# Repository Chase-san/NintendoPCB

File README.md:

# NintendoPCB

This repository is for the reproduction and documentation of various Nintendo PCBs. Specifically targeting the Gameboy series of handheld consoles.

# License

These boards are released under the Creative Commons Attribution-NonCommercial-ShareAlike 4.0 International License. See the LICENSE for more details.

In short, don't sell these designs or boards produced from these designs, and do attribute the designs to me.

# Gameboy GamePak PCB Designs

At present these are designed as repair boards for the official Nintendo Gameboy games. The intention is for the components from the original pcb to be transplanted directly to these boards. However a list of parts is made available if these are not otherwise available. These boards are designed to closely replicate the original tracks and fill zones of the original. These do NOT have the intention of fooling others into thinking they are official boards.

These are NOT designed to be used for Flash Carts, but rather to repair official games.
Please see HDR's [MBC3-Flashcart](https://github.com/HDR/MBC3-Flashcart) and [MBC30-Flashcart](https://github.com/HDR/MBC30-Flashcart) for PCB designs useful as flashcarts.

## Nintendo Board ID

Nintendo uses roughly the following system for producing the ID for a board.

`SYSTEM-ID-REVISION`

`SYSTEM` is either DMG or more rarely GBC, referring to the original Gameboy or the Gameboy Color.

`ID` is the actual ID of the board.

`REVISION` is the revision of the board. Most boards only have a single revision in the wild, but others, such as the DMG-BEAN have up to 6. Every revision I have seen has been electronically compatible with minor track, via, or fill differences.

## Differences from Official PCB

Each of these may have several revisions by Nintendo, I will usually try to base my board off the latest revision where possible. Despite this there are significant differences in design in a few regards compared to official PCBS.

### Debug Tracks and Holes

The Official PCBs make use of tracks which are interconnected, but which are then drilled out. I am unsure of the exact purpose of these, but they were likely for grounding purposes during manufacturing. Most of these have been removed as they serve no purposes for the repair board.
While it is possible that these extra tracks may allow special RF interactions, this does not appear to be by design.

### Thermal Relief

The Official PCBs make use of a different thermal relief pattern than KiCAD. Replicating the factory thermal relief pattern is possible but time consuming. Therefore these are often changed to the method KiCAD uses. Additionally some components may have had thermal relief added where it may be reasonable to do so.

### Identifying Marks

Some of these have been removed or altered.

- The revision number has been changed from a two digit number to "R#" where # is the repair board revision.
- The text "Repair Board" has been added near the board identifier.
- My initials and the year and month of the design have been added.
- Some non-informative identifying marks have been removed. Such as the large numbers on the front of the boards and the circle markers for the date identifier boxes.

### Tracks and Fill

While I make an effort to closely replicate the original board, some features may not be identical to the original. Some features are non-trivial to replicate and therefore an approximation has been used instead.

The main example of this being the battery fill which is fully circular on the repair boards.

## Ordering / Using the Gerber Files

I highly recommend using a service such as [JLCPCB](https://jlcpcb.com/) to get these manufactured. The following are the options that should be selected.

- Layers: 2
- Dimensions: 51mm x 60.7mm / 2" x 2.39"
- PCB Thickness: 0.8mm / 0.0315" (required)
- Surface Finish: ENIG or Hard Gold (required)
- Gold Fingers: Yes (required)
- Finger Chamfer: 45° (recommended)
- Copper Weight: 1 oz or higher (recommended)
- Color: Green (suggested), other colors have longer lead times

Of note, Hard Gold is very expensive so ENIG is a good option. The thicker the layer of gold the better the longer the pins will last. A heavier copper weight is nice but not required.

## Board List

These are the boards. Please check your original for the required one. Only boards with a revision number have a repair board developed.

Each folder related to this project is a distinct KiCAD project, containing subfolders with images of the repair board and scans of the original board it was based on.

This list is NOT exhaustive.

| Revision | ID       | MBC    | ROM      | RAM      | Battery | Other        |
| :------: | :------- | :----: | :----:   | :------: | :-----: | :----------- |
|          | CGB-A32  | MBC-6  | SOP-32   | SOP-28   | CR1616  | Flash        |
| [R3](https://github.com/Chase-san/NintendoPCB/releases/tag/dmg-a02-r3) | DMG-A02  | MBC-5  | SOP-32   | SOP-28   | CR1616  |              |
|          | DMG-A03  | MBC-5  | TSOP2-44 | SOP-28   | CR1616  |              |
|          | DMG-A04  | MBC-5  | TSOP-32  | SOP-28   | CR1616  | Rumble       |
|          | DMG-A06  | MBC-5  | SOP-32   | SOP-28   | CR1616  |              |
|          | DMG-A07  | MBC-5  | SOP-32   | N/A      | N/A     |              |
|          | DMG-A08  | MBC-5  | TSOP2-44 | SOP-28   | CR1616  |              |
|          | DMG-A09  | MBC-5  | TSOP2-44 | N/A      | N/A     |              |
|          | DMG-A11  | MBC-5  | TSOP2-44 | SOP-28   | CR1616  | Rumble       |
|          | DMG-A14  | MBC-5  | TSOP2-44 | SOP-28   | CR2025  |              |
|          | DMG-A15  | MBC-5  | TSOP2-44 | SOP-28   | CR2025  | 2x ROM       |
|          | DMG-A16  | MBC-5  | SOP-32   | SOP-32   | CR2025  |              |
|          | DMG-A40  | MBC-7  | SOP-32   | N/A      | N/A     | Tilt/EEPROM  |
|          | DMG-A47  | MBC-7  | TSOP2-44 | N/A      | N/A     | Tilt/EEPROM  |
| [R1](https://github.com/Chase-san/NintendoPCB/releases/tag/dmg-aaa-r1) | DMG-AAA  | N/A    | MQFP-44  | N/A      | N/A     |              |
|          | DMG-BBA  | MBC-1  | SOIC-24  | N/A      | N/A     |              |
|          | DMG-BEAN | MBC-1  | SOP-32   | N/A      | N/A     |              |
|          | DMG-BFAN | MBC-1  | SOP-32   | N/A      | N/A     |              |
|          | DMG-DECN | MBC-1  | SOP-32   | SOP-28   | CR1616  |              |
|          | DMG-DEDN | MBC-1  | SOP-32   | SOP-28   | CR1616  |              |
|          | DMG-DGCU | MBC-1  | TSOP2-44 | SOP-28   | CR1616  |              |
| [R1](https://github.com/Chase-san/NintendoPCB/releases/tag/dmg-gdan-r1) | DMG-GDAN | MBC-2  | SOP-32   | SOP-28   | CR1616  |              |
|          | DMG-KECN | MBC-3  | SOP-32   | SOP-28   | CR2025  | Clock        |
|          | DMG-KFCN | MBC-3  | SOP-32   | SOP-28   | CR2025  | Clock        |
|          | DMG-KFDN | MBC-3  | SOP-32   | SOP-28   | CR2025  | Clock        |
| [R4](https://github.com/Chase-san/NintendoPCB/releases/tag/dmg-kgdu-r4) | DMG-KGDU | MBC-3  | TSOP2-44 | SOP-28   | CR2025  | Clock        |
|          | DMG-LFDN | MBC-3  | SOP-32   | SOP-28   | CR2025  | Clock        |
|          | DMG-MHEU | MBC-30 | TSOP2-44 | SOP-28   | CR2025  | Clock        |
|          | DMG-TEDN | HuC-1  | SOP-32   | SOP-28   | CR1616  | IR           |
|          | DMG-TFDN | HuC-1  | SOP-32   | SOP-28   | CR1616  | IR           |
|          | DMG-UEDT | HuC-3  | TSOP1-32 | TSOP1-28 | CR2025  | IR/Clock     |
|          | DMG-UFDT | HuC-3  | TSOP1-32 | TSOP1-28 | CR2025  | IR/Clock     |
|          | DMG-UGDU | HuC-3  | TSOP2-44 | TSOP1-28 | CR2025  | IR/Clock     |
|          | DMG-Z02  | MBC-5  | SOP-32   | SOP-28   | CR1616  |              |
|          | DMG-Z03  | MBC-5  | TSOP2-44 | SOP-28   | CR1616  |              |
|          | DMG-Z04  | MBC-5  | TSOP2-44 | SOP-28   | CR1616  | Rumble       |

# Game Usage

Here is a list of the primary games using the given boards. Some boards have a lot of games or the game that uses the board is not particularly popular. Some games have used multiple boards (mostly pokemon).

| ID        | Main Usage  |
| :-------  | :---------  |
| CGB-A32   | Net de Get - Minigame @ 100 (Japan) |
| DMG-A02   | Pokemon Red/Blue, Lots of other games. |
| DMG-A03   | Wario Land 2/3 |
| DMG-A04   | Pokemon Pinball |
| DMG-A06   | Game & Watch, Mega Man Xtreme 2 |
| DMG-A07   |  |
| DMG-A08   | TLOZ: Oracle of Ages/Seasons  |
| DMG-A09   | Rayman, Tony Hawk Pro Skater 2 |
| DMG-A11   | Pokemon Pinball  |
| DMG-A14   |  |
| DMG-A15   |  |
| DMG-A16   |  |
| DMG-A40   | Kirby Tilt & Tumble  |
| DMG-A47   |  |
| DMG-AAA   | Catrap, Dr. Mario, Tetris  |
| DMG-BBA   |  |
| DMG-BEAN  | Mega Man II-V, Pacman |
| DMG-BFAN  | Mortal Kombat I/II |
| DMG-DECN  | Donkey Kong, Donkey Kong Land, Super Mario Land 2  |
| DMG-DEDN  | Pocket Monsters Aka, Midori (Japan) |
| DMG-DGCU  | Dragon Quest Monsters  |
| DMG-GDAN  | Kirby's Pinball Land |
| DMG-KECN  | Bokujou Monogatari GB  |
| DMG-KFCN  | Mary Kate & Ashley Pocket Planner |
| DMG-KFDN  | Pokemon Gold/Silver/Crystal  |
| DMG-KGDU  | Pokemon Gold/Silver/Crystal  |
| DMG-LFDN  | Pocket Monsters Pikachu (Japan) |
| DMG-MHEU  | Pokemon Crystal (Japan)  |
| DMG-TEDN  | Pocket Bomber Man (Japan) |
| DMG-TFDN  | Pokemon Card GB (Japan) |
| DMG-UEDT  | Pocket Family GB  |
| DMG-UFDT  | Pocket Family GB  |
| DMG-UGDU  | Pocket Family GB 2  |
| DMG-Z02   | Mega Man Xtreme |
| DMG-Z03   |  |
| DMG-Z04   | Pokemon Pinball  |

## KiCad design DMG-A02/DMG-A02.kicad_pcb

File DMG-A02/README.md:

# DMG-A02

This board is a repair board based on the DMG-A02-10. The DMG-A02 is used by german versions of Pokemon Red/Blue, as well as Pokemon Yellow, Pokemon Trading Card Game, and Link's Awakening DX.

The original featured cut holes that were used for debugging purposes, most of these have been omitted.

This board was designed to closely replicate the footprints and routes used by the original cartridge board. All components may be sourced from an original cart.

## Components

This board features a 32-pin ROM and a 28-pin RAM module.

| Ref   | Package     | Description  | Notes | 
| :---: | :---------: | :----------- | :---- |
| U1    | SSOP-32W    | Program ROM  | ~11mm wide |
| U2    | LQFP-32     | MBC-5        | |
| U3    | SOIC-28W    | SRAM         | ~8.3mm wide |
| U4    | SOIC-28     | System Reset | ~4.3mm wide |
| C1, C2, C3, C4 | 0603 (in)   |  0.015uF - 0.1uF Capacitor | |
| C5    | 0603 (in)   | Empty | |
| C6    | 0603 (in)   | 33pF Capacitor | May be left empty |
| R1    | 0603 (in)   | 1kOhm Resistor | |

## Change Log

### R4 (2023-02-13)
- Added teardrop to pin pads.
- Adjusted MBC cutout
- Other minor changes

### R3 (2023-01-23)
- Added teardrops to via.
- Fillet tracks
- Added MBC hole

### Rev2 (2023-01-21)
- Fixed rear GND Test pad.

### Rev1 (2023-01-20)
- Initial build

## Images

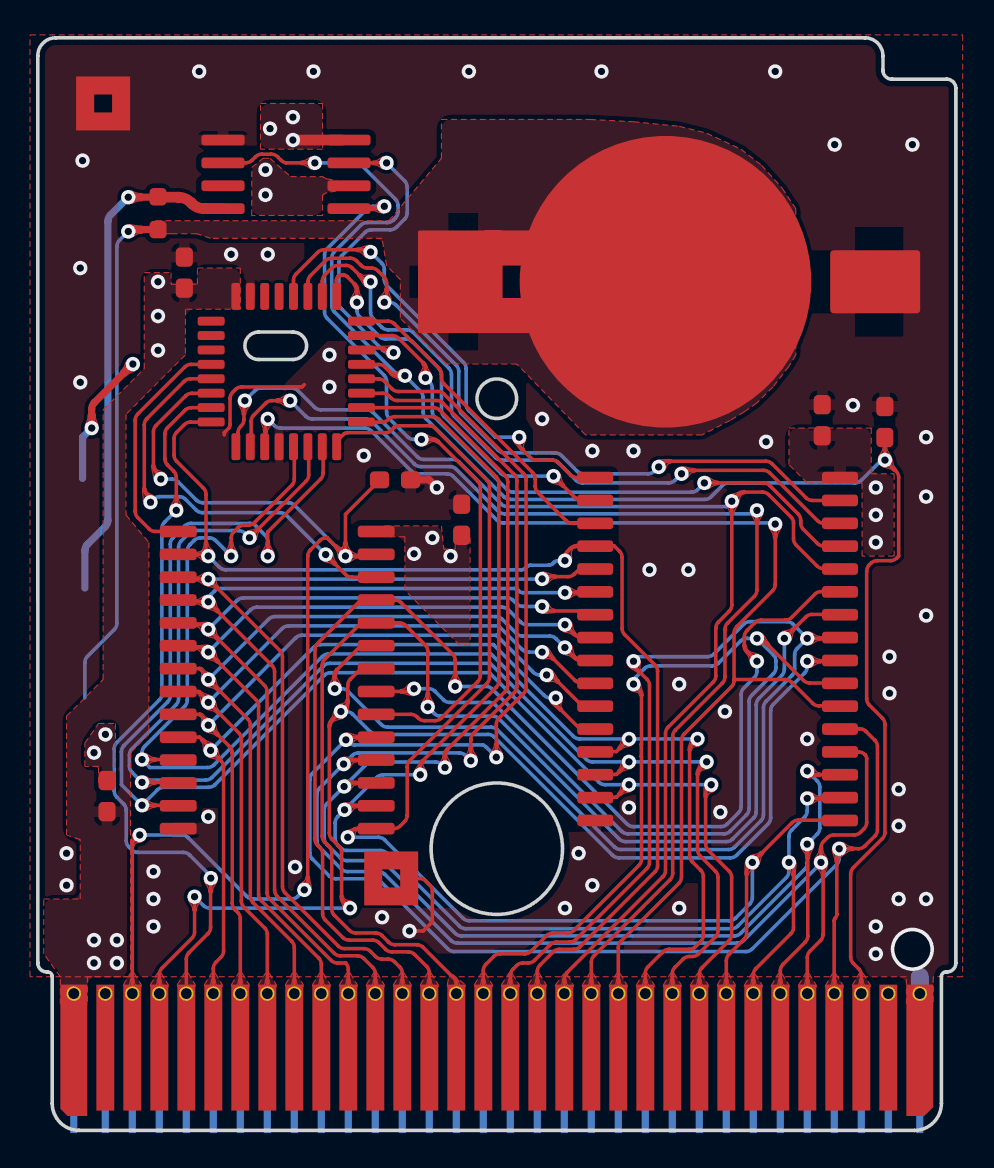
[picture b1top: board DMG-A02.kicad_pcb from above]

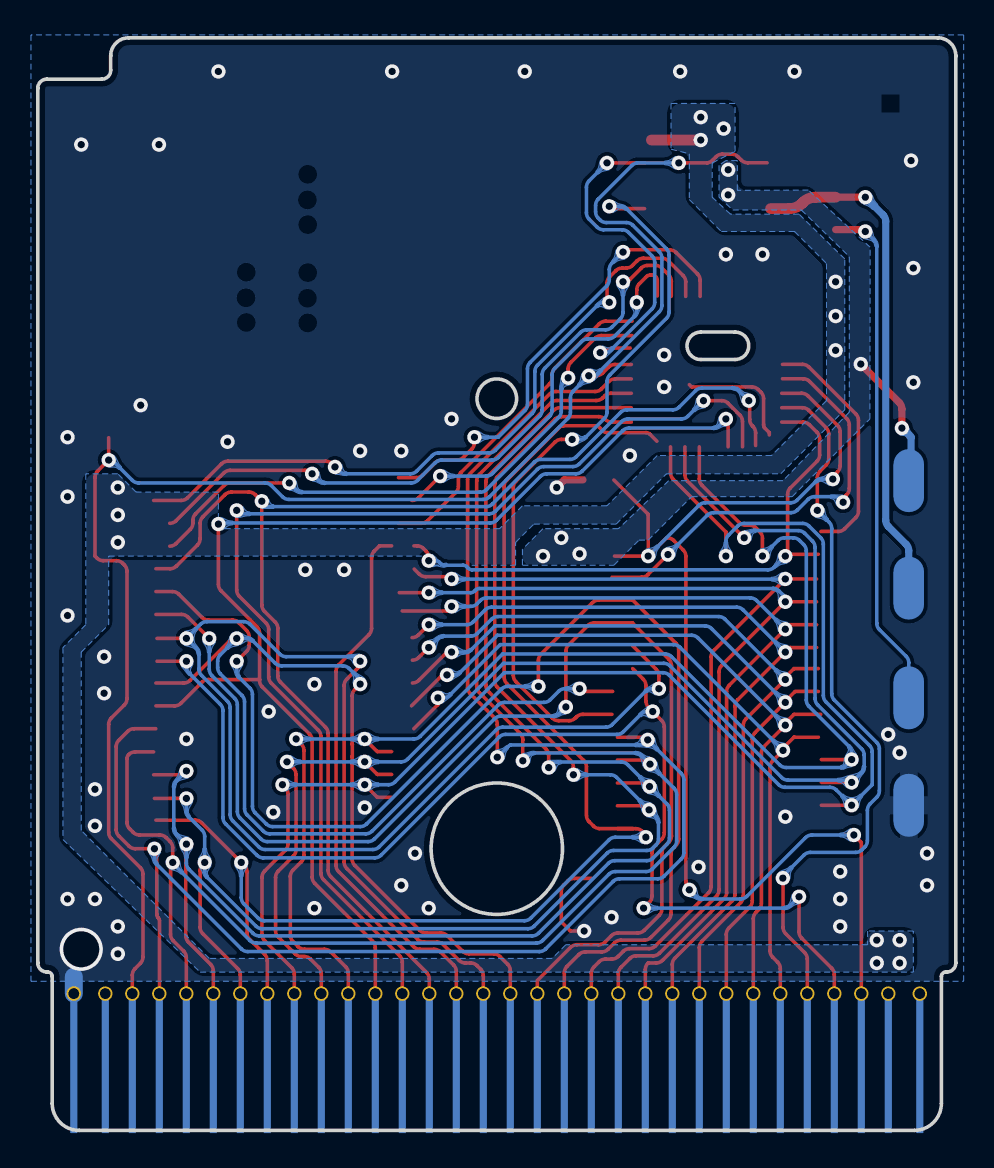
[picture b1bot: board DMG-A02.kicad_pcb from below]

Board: 2 copper layers, 51.0 x 60.7 mm, 19 parts (4 on the bottom side), 43 nets.

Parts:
BATT1: Batt_CR1616
C1, C2, C3, C4, C5, C6: 0.1uF; C_0603_Pad_HandSolder
G1, G2: GroundPad_Square_SMD_3mm
R1: 1kΩ; R_0603_Pad_HandSolder
TP1, TP2, TP3, TP4: TestPoint_3.5x1.7mm
U0: CartBus; GameBoy_GamePak_CGB-002_P1.50mm_Edge
U1: SSOP-32_MROM
U2: LQFP-32_MBC
U3: SOIC-28_SRAM
U4: SO-8_SYSRST

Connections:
A00: U0.6, U1.12, U3.10
A01: U0.7, U1.11, U3.9
A02: U0.8, U1.10, U3.8
A03: U0.9, U1.9, U3.7
A04: U0.10, U1.8, U3.6
A05: U0.11, U1.7, U3.5
A06: U0.12, U1.6, U3.4
A07: U0.13, U1.5, U3.3
A08: U0.14, U1.27, U3.25
A09: U0.15, U1.26, U3.24
A10: U0.16, U1.23, U3.21
A11: U0.17, U1.25, U3.23
A12: U0.18, U1.4, U2.32, U3.2
A13: U0.19, U1.28, U2.1
A14: U0.20, U2.2
A15: U0.21, U1.22, U2.3
BT+: BATT1.1, R1.1, TP3.1
CS: U0.5, U2.31
CS_EN: U2.14, U4.7
D0: U0.22, U1.13, U2.5, U3.11
D1: U0.23, U1.14, U2.6, U3.12
D2: U0.24, U1.15, U2.7, U3.13
D3: U0.25, U1.17, U2.8, U3.15
D4: U0.26, U1.18, U2.9, U3.16
D5: U0.27, U1.19, U2.10, U3.17
D6: U0.28, U1.20, U2.11, U3.18
D7: U0.29, U1.21, U2.12, U3.19
GND: BATT1.2, C1.2, C2.2, C3.2, C4.2, C5.2, C6.2, G1.1, G2.1, TP4.1, U0.32, U1.16, U2.4, U2.23, U3.14, U4.1
RA14: U1.29, U2.15
RA15: U1.3, U2.16
RA16: U1.2, U2.17
RA17: U1.30, U2.18
RA18: U1.31, U2.19
RA19: U1.1, U2.20
RAMCS: U3.20, U4.5
Read: U0.4, U1.24, U3.22
Reset: C5.1, U0.30, U2.13, U4.2
SA13: U2.29, U3.26
SA14: U2.28, U3.1
VBATT: R1.2, TP2.1, U4.4
VCC: C1.1, C2.1, C4.1, U0.1, U1.32, U2.24, U4.8
VOUT: C3.1, TP1.1, U3.28, U4.6
Write: C6.1, U0.3, U2.30, U3.27

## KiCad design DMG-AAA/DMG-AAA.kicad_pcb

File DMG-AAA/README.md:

# DMG-AAA

This board is a repair board based on the DMG-AAA-02. The DMG-AAA is used by Catrap, Dr. Mario, and most versions of Tetris.

This board does not feature a MBC at all, and only has a ROM chip.

The original featured cut holes that were used for debugging or reference purposes, these have been mostly preserved.

This board was designed to closely replicate the footprints and routes used by the original cartridge board.

## Components

This board features a 44-pin ROM.

| Ref   | Package     | Description  | Notes | 
| :---: | :---------: | :----------- | :---- |
| U1    | MQFP-44     | Program ROM  | |
| C1    | Axial 3.8mm x 2mm    | 10nF ±10% Capacitor | Might be empty |
| C2    | Radial 6.8mm x 2.8mm | | Usually Empty |

## Change Log

### R2 (2023-02-03)
- Added missing pointer.

### R1 (2023-02-02)
- Initial build

## Images

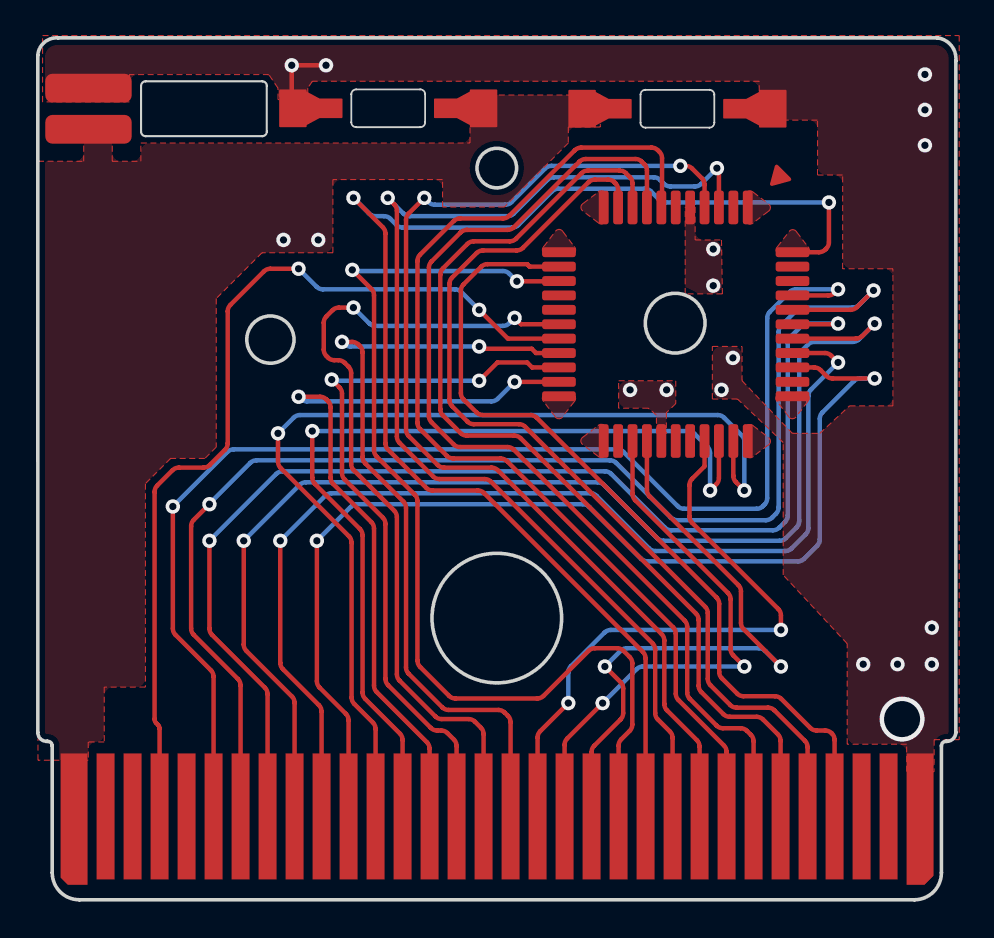
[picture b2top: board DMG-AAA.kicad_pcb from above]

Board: 2 copper layers, 51.0 x 47.9 mm, 5 parts (0 on the bottom side), 27 nets.

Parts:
C1, C1#2: Capacitor_SMD_Axial_4mm; Capacitor_SMD_Axial_4mm_2mm
C2: C_Radial_Pad_7mm_x_3mm
U0: CartBus; Connector_Edge_GamePak_P1.50mm
U1: PRG; MQFP-44_10x10mm_P0.8mm

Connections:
A00: U0.6, U1.41
A01: U0.7, U1.40
A02: U0.8, U1.39
A03: U0.9, U1.38
A04: U0.10, U1.37
A05: U0.11, U1.36
A06: U0.12, U1.32
A07: U0.13, U1.31
A08: U0.14, U1.21
A09: U0.15, U1.20
A10: U0.16, U1.17
A11: U0.17, U1.19
A12: U0.18, U1.30
A13: U0.19, U1.25
A14: U0.20, U1.26
A15: U0.21, U1.14
D0: U0.22, U1.44
D1: U0.23, U1.3
D2: U0.24, U1.4
D3: U0.25, U1.7
D4: U0.26, U1.8
D5: U0.27, U1.9
D6: U0.28, U1.10
D7: U0.29, U1.13
GND: C1.2, C1#2.1, C2.1, U0.32, U1.5
VCC: C1.1, C1#2.2, C2.2, U0.1, U1.27
~RD: U0.4, U1.18

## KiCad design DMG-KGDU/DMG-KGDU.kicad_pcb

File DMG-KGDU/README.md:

# DMG-KGDU

This board is a repair board based on the DMG-KGDU-10. The DMG-KGDU is used by the USA versions of Pokemon Gold, Silver, and Crystal.

The original featured cut holes that were used for debugging purposes, these have been omitted.

This board was designed to closely replicate the footprints and routes used by the original cartridge board. All components may be sourced from an original cart.

## Components

This board features a 44-pin ROM and a 28-pin RAM module.

| Ref   | Package     | Description  | Notes | 
| :---: | :---------: | :----------- | :---- |
| U1    | TSOP-II-44W | Program ROM  | ~10.1mm wide |
| U2    | LQFP-32     | MBC-3        | |
| U3    | SOIC-28W    | SRAM         | ~8.3mm wide |
| U4    | SOIC-8      | System Reset | ~4.3mm wide |
| C1,C2 | 0603 (in)   | 15pF Capacitor | |
| C3, C4, C5, C6 | 0603 (in) | 15nF Capacitor | Anything up to 0.1μF is supproted |
| R1    | 0603 (in)   | 1kOhm Resistor | |
| R2    | 0603 (in)   | 330kOhm Resistor | |
| X1    | 6mm x 2mm   | 32.768 kHZ Cystal | 12.5 pF Load and 35 kOhm ESR |

## Change Log

### R4 (2023-02-03)
- Fillet the tracks
- Fix teardrops
- Fix various pad connections.

### Rev3 (2023-01-29)
- Added teardrops to vias and pins. Should help in fabs with lower standards, they also look nicer.
- Modified the X1 no copper zone to better reflect the original boards.
- Rounded the corners of the X1 cutout to be easier to manufacture.
- Removed the last of the silk screen.

### Rev2 (2023-01-21)
- Board redesigned based on high resolution scans.

### Rev1 (2023-01-20)
- Initial build based on photos.

## Images

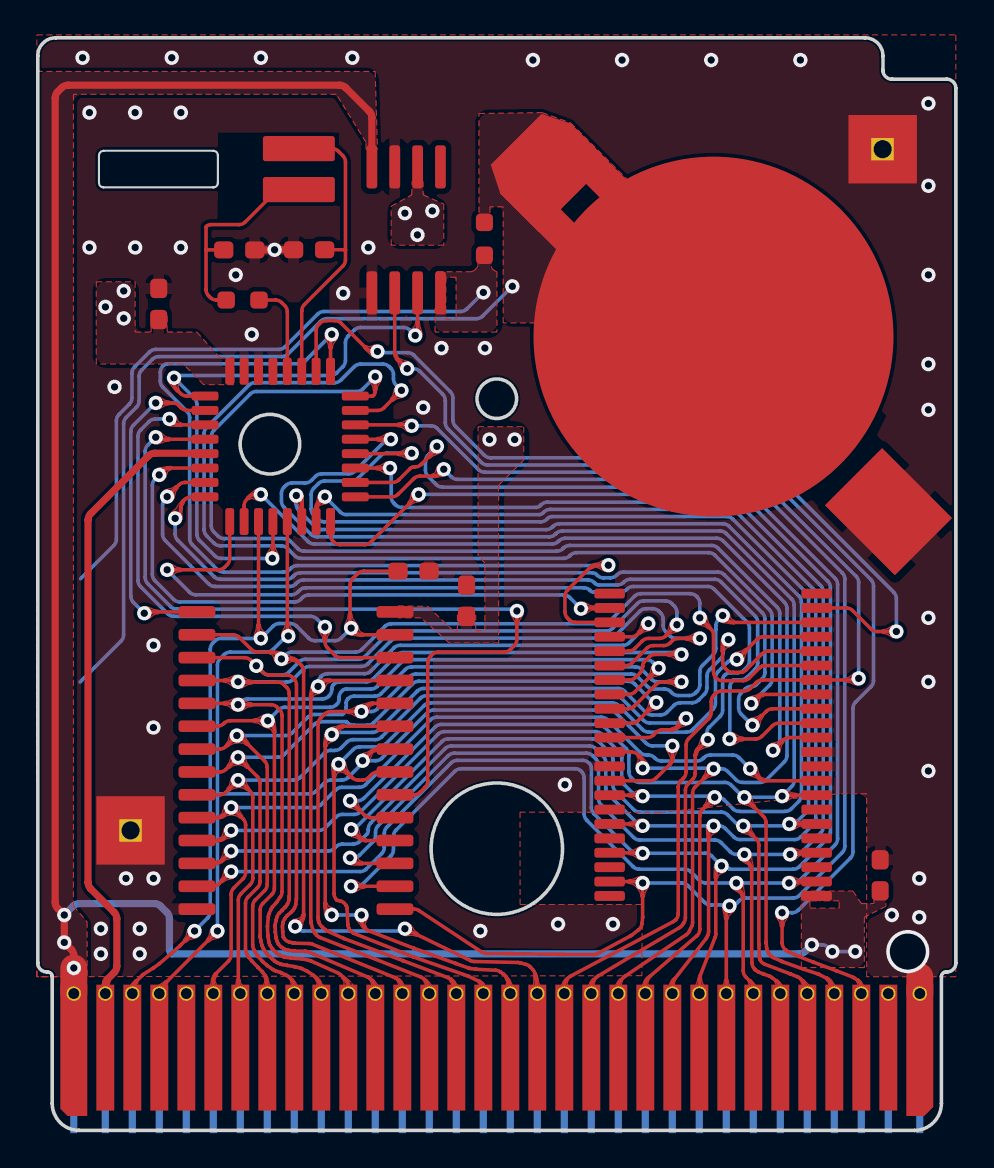
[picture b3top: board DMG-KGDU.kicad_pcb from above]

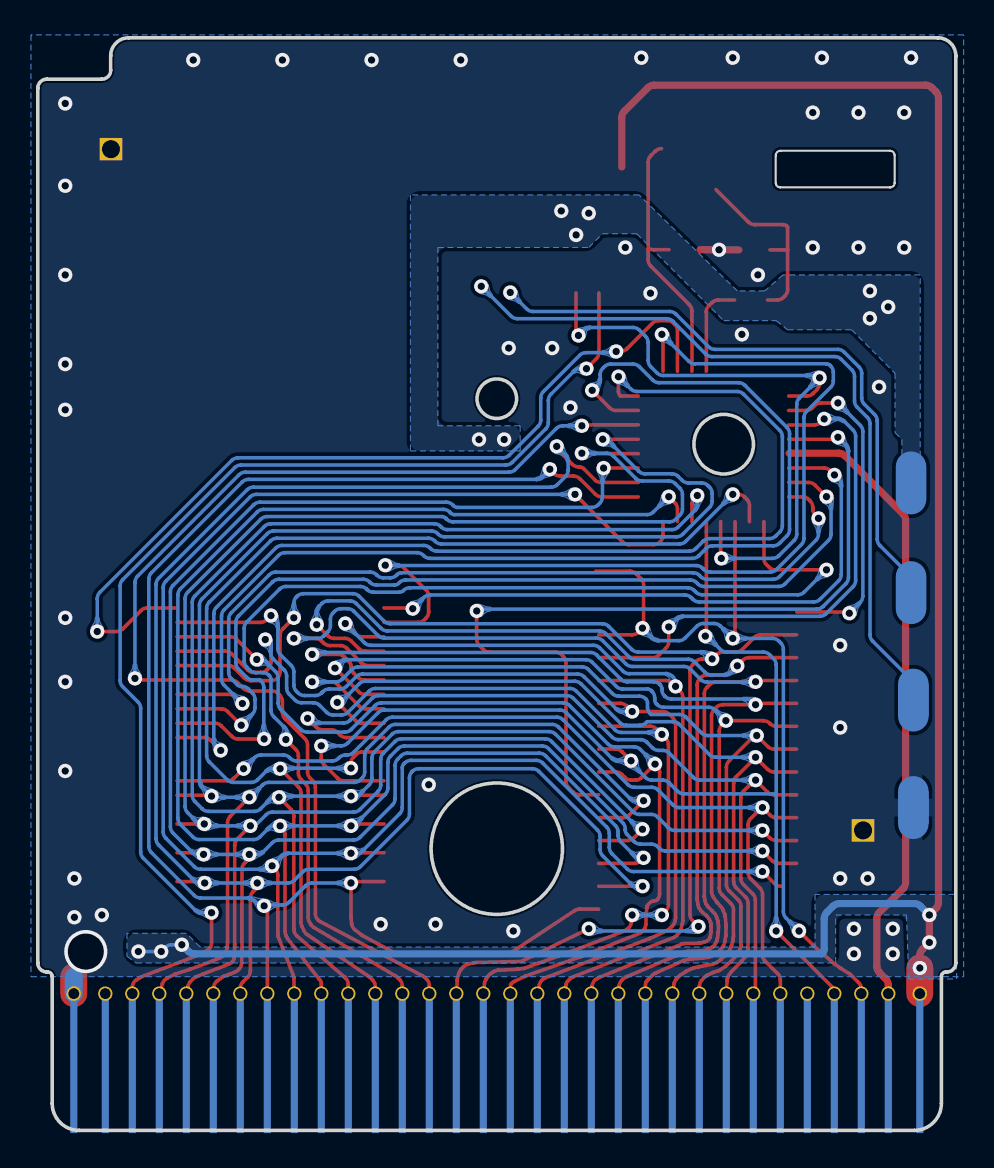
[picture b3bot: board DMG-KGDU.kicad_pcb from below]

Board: 2 copper layers, 51.0 x 60.7 mm, 21 parts (4 on the bottom side), 47 nets.

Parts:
BT1: Batt CR2025; Batt_CR2025
C1, C2: 15pF; C_0603_Pad_HandSolder
C3, C4, C5, C6: 0.1pF; C_0603_Pad_HandSolder
GND1, GND2: GroundPad_Square_TH_3.8mm
R1: 1kΩ; R_0603_Pad_HandSolder
R2: 330kΩ; R_0603_Pad_HandSolder
TP1, TP2, TP3, TP4: TestPoint_3.5x1.7mm
U0: CartBus; GameBoy_GamePak_CGB-002_P1.50mm_Edge
U1: PRG; TSOP-II-44_MROM
U2: MBC3A; LQFP-32_MBC
U3: RAM; SOIC-28_SRAM
U4: MM1134; SO-8_SYSRST
X1: Crystal_D2mm_L6mm_Horizontal

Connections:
A00: U0.6, U1.31, U3.10
A01: U0.7, U1.11, U3.9
A02: U0.8, U1.10, U3.8
A03: U0.9, U1.9, U3.7
A04: U0.10, U1.8, U3.6
A05: U0.11, U1.7, U3.5
A06: U0.12, U1.6, U3.4
A07: U0.13, U1.5, U3.3
A08: U0.14, U1.4, U3.25
A09: U0.15, U1.42, U3.24
A10: U0.16, U1.41, U3.21
A11: U0.17, U1.40, U3.23
A12: U0.18, U1.39, U3.2
A13: U0.19, U1.38, U2.14
A14: U0.20, U2.1
A15: U0.21, U1.12, U2.2
AA13: U2.27, U3.26
AA14: U2.26, U3.1
BT+: BT1.1, R1.2, TP3.1
CE: U2.28, U3.20
Clock: U0.2, U2.29
D0: U0.22, U1.15, U2.6, U3.11
D1: U0.23, U1.17, U2.7, U3.12
D2: U0.24, U1.19, U2.8, U3.13
D3: U0.25, U1.21, U2.9, U3.15
D4: U0.26, U1.24, U2.10, U3.16
D5: U0.27, U1.26, U2.11, U3.17
D6: U0.28, U1.28, U2.12, U3.18
D7: U0.29, U1.30, U2.13, U3.19
GND: BT1.2, C1.1, C2.2, C3.2, C4.2, C5.2, C6.2, GND1.1, GND2.1, TP4.1, U0.32, U1.13, U1.32, U1.33, U2.22, U2.23, U3.14, U4.1, U4.7
RA14: U1.37, U2.15
RA15: U1.36, U2.32
RA16: U1.35, U2.31
RA17: U1.34, U2.16
RA18: U1.3, U2.17
RA19: U1.2, U2.30
RA20: U1.43, U2.18
Read: U0.4, U1.14, U2.5, U3.22
Reset: U0.30, U4.2
SYS_RST: U2.4, U2.25, U4.3
VBATT: R1.1, TP2.1, U4.4
VCC: C3.1, U0.1, U1.23, U4.8
VOUT: C4.1, C5.1, TP1.1, U2.24, U3.28, U4.6
Write: C6.1, U0.3, U2.3, U3.27
XIN: C1.2, U2.19, X1.1
XOUT: R2.2, U2.20
X_: C2.1, R2.1, X1.2

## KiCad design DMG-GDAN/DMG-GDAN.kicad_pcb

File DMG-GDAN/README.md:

# DMG-GDAN-10

This board is a repair board based on the DMG-GDAN-10. The DMG-GDAN is used by F-1 Race, Kirby's Pinball Land, and Ultra Golf.

Unlike the other memory controllers, the MBC2 has ram onboard, preventing the need for an additional RAM chip. This board was mainly used by games that needed saves, but not much additional ram.

The original featured cut holes that were used for debugging or reference purposes, these have been omitted.

This board was designed to closely replicate the footprints and routes used by the original cartridge board.

## Components

This board features a 32-pin ROM. Like many boards before the MBC-3 this one features components that can be both axial/radial or SMD.

| Ref   | Package     | Description  | Notes | 
| :---: | :---------: | :----------- | :---- |
| U1    | SOP-32      | Program ROM  | |
| U2    | SOIC-28W    | MBC-2        | |
| U3    | SOIC-28     | System Reset | |
| C1    | Axial & 0603 | 10nF ±10% Capacitor | Only populate one |
| C2    | Axial & 0603 | 10nF ±10% Capacitor | Only populate one |
| C3    | Radial & 0603 | | Usually empty |
| R1    | Axial & 0603 | 10K Ohm 5% Resistor | Only populate one |

## Change Log

### R1 (2023-02-02)
- Initial build

## Images

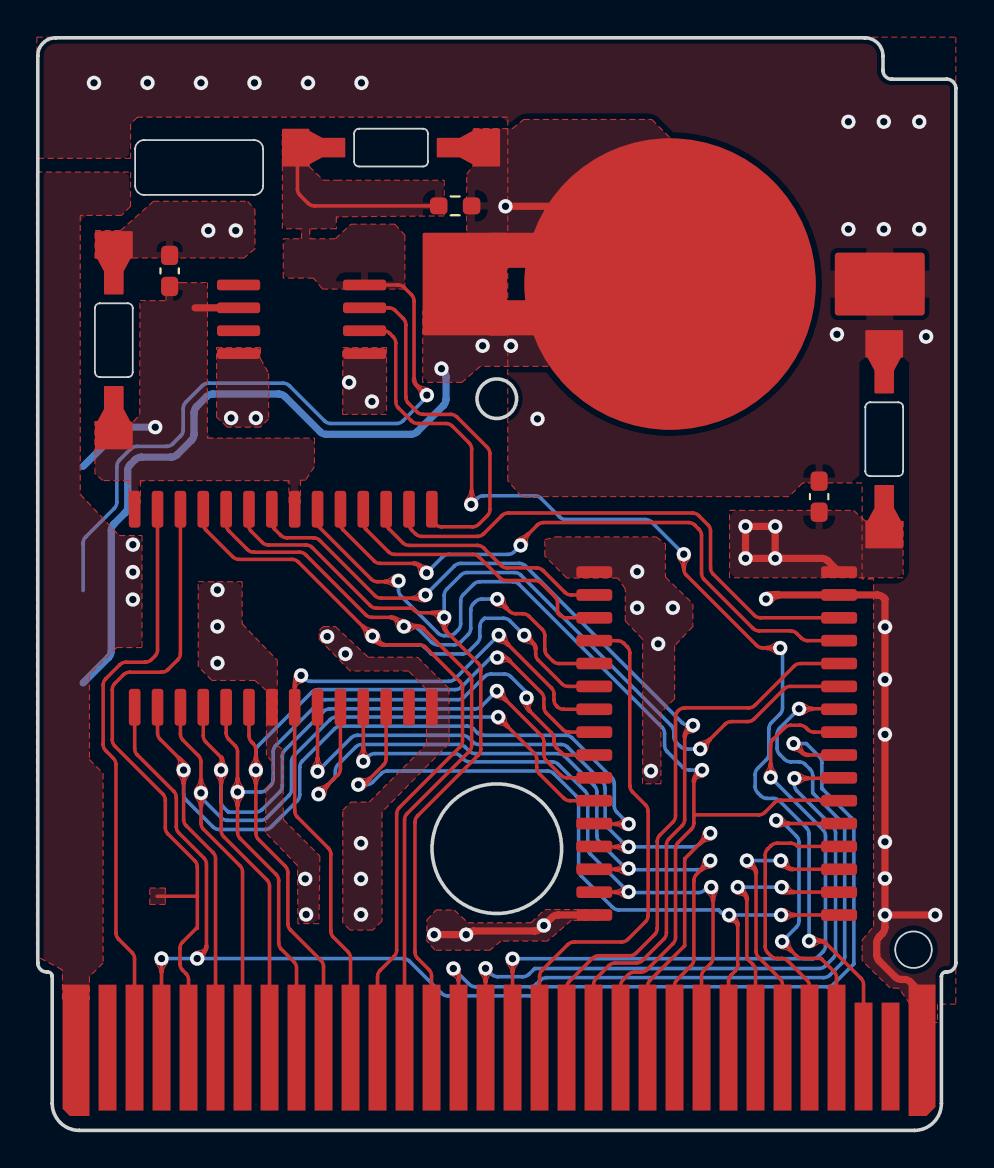
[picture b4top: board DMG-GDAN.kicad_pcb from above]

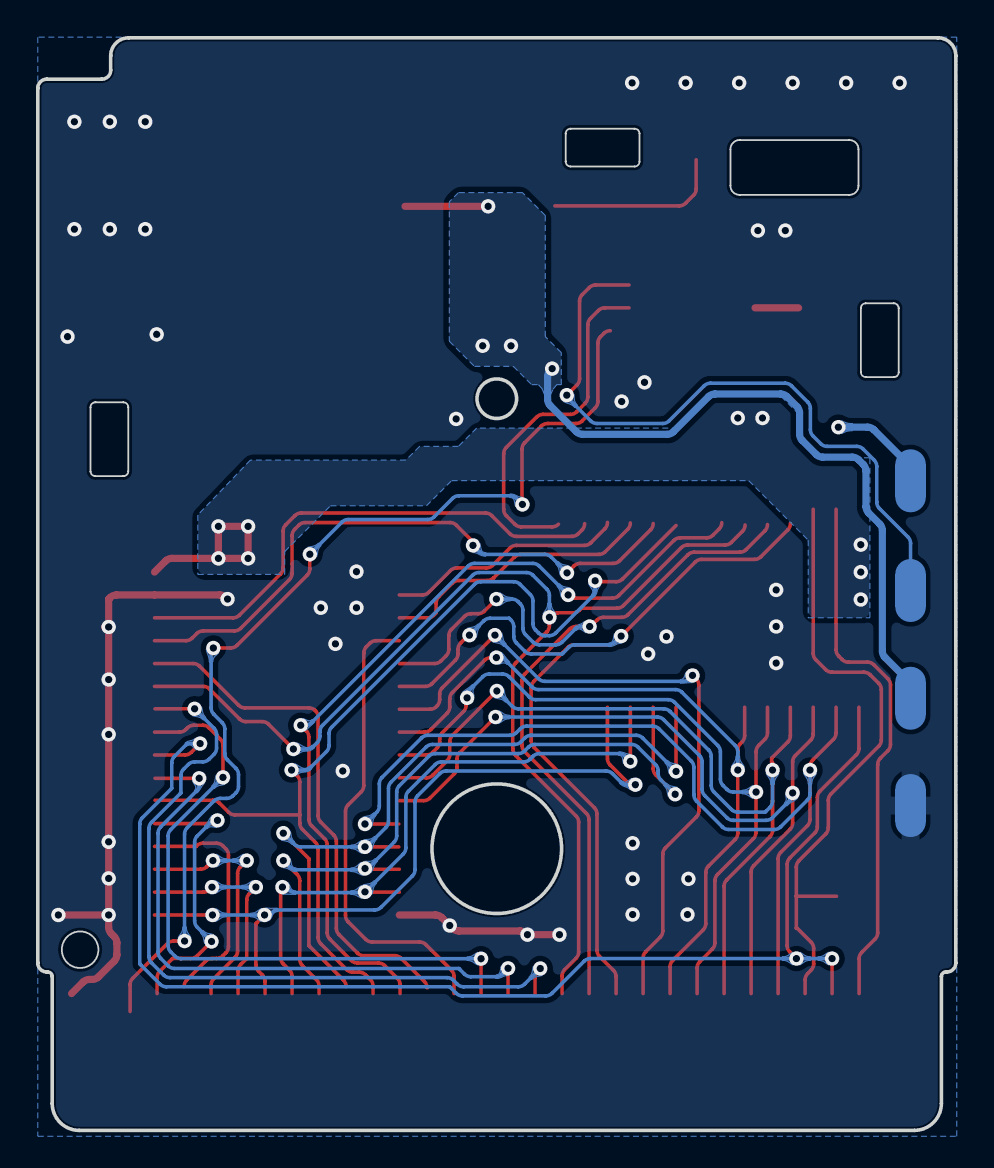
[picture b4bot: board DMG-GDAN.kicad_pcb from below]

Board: 2 copper layers, 51.0 x 60.7 mm, 15 parts (4 on the bottom side), 38 nets.

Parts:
( R1 ): Resistor_SMD_Axial_4mm_2mm
(C1), (C2): Capacitor_SMD_Axial_4mm; Capacitor_SMD_Axial_4mm_2mm
Batt: CR1616; Batt_CR1616
C1, C2: C_0603_1608Metric_Pad1.08x0.95mm_HandSolder
R1: R_0603_1608Metric_Pad0.98x0.95mm_HandSolder
TP1, TP2, TP3, TP4: TestPoint_3.5x1.7mm
U0: CartBus; Connector_Edge_GamePak_P1.50mm
U1: PRG; SSOP-32_MROM
U2: MBC2A; SOIC-28_SRAM
U3: 26A; SO-8_SYSRST

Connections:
A00: U0.6, U1.12, U2.2
A01: U0.7, U1.11, U2.3
A02: U0.8, U1.10, U2.4
A03: U0.9, U1.9, U2.5
A04: U0.10, U1.8, U2.6
A05: U0.11, U1.7, U2.8
A06: U0.12, U1.6, U2.25
A07: U0.13, U1.5, U2.24
A08: U0.14, U1.27, U2.23
A09: U0.15, U1.26
A10: U0.16, U1.23
A11: U0.17, U1.25
A12: U0.18, U1.4
A13: U0.19, U1.28
A14: U0.20, U2.22
A15: U0.21, U1.22, U2.20
BT+: ( R1 ).2, Batt.1, R1.2, TP3.3
CS: U0.5, U2.26
CS_U3: U2.15, U3.3
D0: U0.22, U1.13, U2.9
D1: U0.23, U1.14, U2.10
D2: U0.24, U1.15, U2.11
D3: U0.25, U1.17, U2.12
D4: U0.26, U1.18
D5: U0.27, U1.19
D6: U0.28, U1.20
D7: U0.29, U1.21
GND: (C1).2, (C2).2, Batt.2, C1.2, C2.2, TP4.4, U0.32, U1.1, U1.16, U1.31, U2.7, U2.14, U3.1
RA14: U1.29, U2.19
RA15: U1.3, U2.18
RA16: U1.2, U2.17
RA17: U1.30, U2.16
VBAT: ( R1 ).1, R1.1, TP2.2, U3.4
VCC: (C1).1, C1.1, U0.1, U1.32, U3.8
VOUT: (C2).1, C2.1, TP1.1, U2.21, U2.28, U3.6
/RD: U0.4, U1.24, U2.1
/RST: U0.30, U3.2
/WR: U0.3, U2.27

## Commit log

2023-03-01 Remake due to GIT-LFS issues
2023-03-01 Update capacitor values.
2023-03-01 Fix D3 arc issue
2023-03-01 Update timestamp.

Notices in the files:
DMG-A02/DMG-A02.kicad_pcb:
©1998
DMG-AAA/DMG-AAA.kicad_pcb:
© 1989
DMG-KGDU/DMG-KGDU.kicad_pcb:
©2000
